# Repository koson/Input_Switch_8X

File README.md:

# Input_Switch_8X

## Schematic

## 3D render

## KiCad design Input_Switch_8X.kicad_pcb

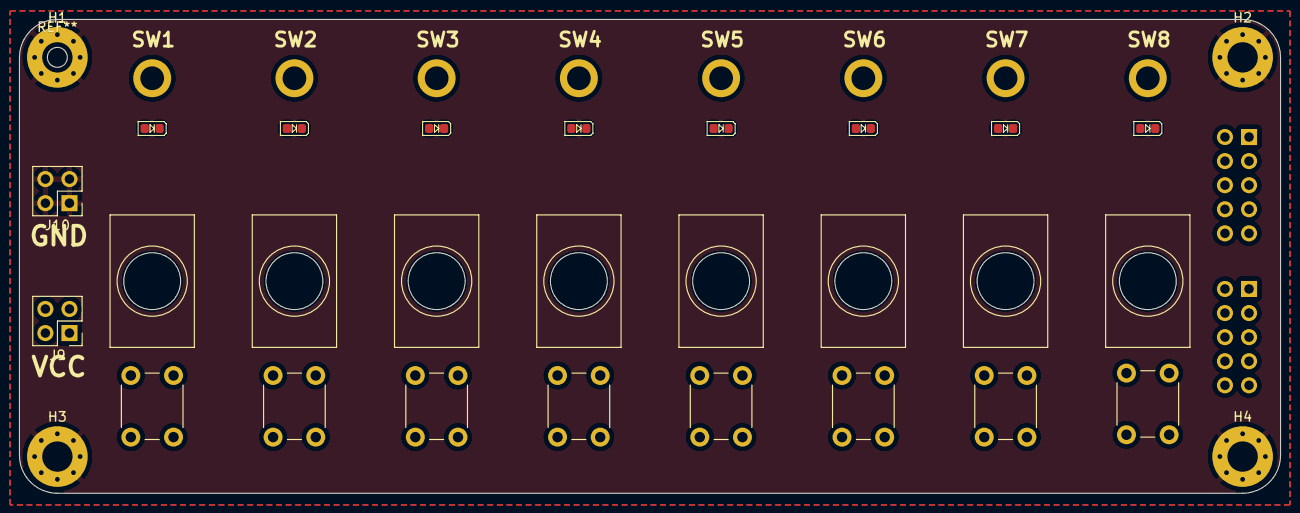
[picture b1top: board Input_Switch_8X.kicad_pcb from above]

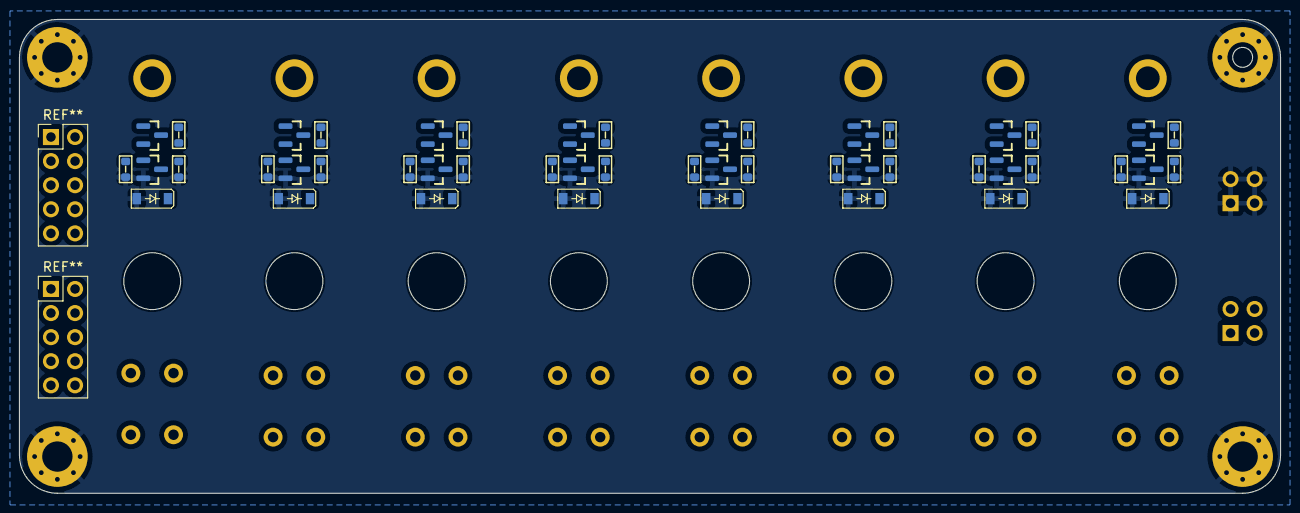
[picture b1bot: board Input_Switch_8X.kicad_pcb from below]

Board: 2 copper layers, 133.0 x 50.0 mm, 86 parts (48 on the bottom side), 34 nets, no tracks yet.

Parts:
D1, D4, D6, D8, D10, D12, D14, D16: LED; LED_0603_1608Metric
D2, D3, D5, D7, D9, D11, D13, D15: BZT52C10; D_SOD-123
H1, H2, H3, H4: MountingHole_Pad; MountingHole_3.2mm_M3_Pad_Via
J1, J2, J3, J4, J5, J6, J7, J8: Conn_01x02; MountingHole_2.5mm_Pad
J9: VCC; PinHeader_2x02_P2.54mm_Vertical
J10: GND; PinHeader_2x02_P2.54mm_Vertical
Q1, Q4, Q6, Q8, Q10, Q12, Q14, Q16: AO3400A; SOT-23
Q2, Q3, Q5, Q7, Q9, Q11, Q13, Q15: BC817; SOT-23
R1, R2, R3, R4, R15, R18, R21, R24: 33R; R_0603_1608Metric
R5, R8, R10, R12, R14, R17, R20, R23: 1k; R_0603_1608Metric
R6, R7, R9, R11, R13, R16, R19, R22: 10k; R_0603_1608Metric
SW1, SW3, SW5, SW7, SW9, SW11, SW13, SW15: SW_Push; SW_PUSH_6mm_H5mm
SW2, SW4, SW6, SW8, SW10, SW12, SW14, SW16: SW_SPST; SW_Toggle_Blue_wSlots_Nut

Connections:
/Switch_LED_1/Output: J1.1, R5.2, R6.1, SW1.2
/Switch_LED_2/Output: J2.1, R7.1, R8.2, SW3.2
/Switch_LED_3/Output: J3.1, R9.1, R10.2, SW5.2
/Switch_LED_4/Output: J4.1, R11.1, R12.2, SW7.2
/Switch_LED_5/Output: J5.1, R13.1, R14.2, SW9.2
/Switch_LED_6/Output: J6.1, R16.1, R17.2, SW11.2
/Switch_LED_7/Output: J7.1, R19.1, R20.2, SW13.2
/Switch_LED_8/Output: J8.1, R22.1, R23.2, SW15.2
GND: D2.2 (A), D3.2 (A), D5.2 (A), D7.2 (A), D9.2 (A), D11.2 (A), D13.2 (A), D15.2 (A), H1.1, H2.1, H3.1, H4.1, J10.1, J10.2, J10.3, J10.4, Q2.2 (E), Q3.2 (E), Q5.2 (E), Q7.2 (E), Q9.2 (E), Q11.2 (E), Q13.2 (E), Q15.2 (E), R1.2, R2.2, R3.2, R4.2, R6.2, R7.2, R9.2, R11.2, R13.2, R15.2, R16.2, R18.2, R19.2, R21.2, R22.2, R24.2
unnamed: D1.1 (K), Q1.3 (D)
unnamed: D2.1 (K), Q1.1 (G), Q2.3 (C), R5.1
unnamed: D3.1 (K), Q3.3 (C), Q4.1 (G), R8.1
unnamed: D4.1 (K), Q4.3 (D)
unnamed: D5.1 (K), Q5.3 (C), Q6.1 (G), R10.1
unnamed: D6.1 (K), Q6.3 (D)
unnamed: D7.1 (K), Q7.3 (C), Q8.1 (G), R12.1
unnamed: D8.1 (K), Q8.3 (D)
unnamed: D9.1 (K), Q9.3 (C), Q10.1 (G), R14.1
unnamed: D10.1 (K), Q10.3 (D)
unnamed: D11.1 (K), Q11.3 (C), Q12.1 (G), R17.1
unnamed: D12.1 (K), Q12.3 (D)
unnamed: D13.1 (K), Q13.3 (C), Q14.1 (G), R20.1
unnamed: D14.1 (K), Q14.3 (D)
unnamed: D15.1 (K), Q15.3 (C), Q16.1 (G), R23.1
unnamed: D16.1 (K), Q16.3 (D)
unnamed: Q1.2 (S), Q2.1 (B), R1.1
unnamed: Q3.1 (B), Q4.2 (S), R2.1
unnamed: Q5.1 (B), Q6.2 (S), R3.1
unnamed: Q7.1 (B), Q8.2 (S), R4.1
unnamed: Q9.1 (B), Q10.2 (S), R15.1
unnamed: Q11.1 (B), Q12.2 (S), R18.1
unnamed: Q13.1 (B), Q14.2 (S), R21.1
unnamed: Q15.1 (B), Q16.2 (S), R24.1
VCC: D1.2 (A), D4.2 (A), D6.2 (A), D8.2 (A), D10.2 (A), D12.2 (A), D14.2 (A), D16.2 (A), J9.1, J9.2, J9.3, J9.4, SW1.1, SW3.1, SW5.1, SW7.1, SW9.1, SW11.1, SW13.1, SW15.1

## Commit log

2022-10-19 add gerber files
2022-10-19 update footprint
2022-10-19 update gerber
2024-05-03 dev1
2024-05-03 Remove the now ignored directory
